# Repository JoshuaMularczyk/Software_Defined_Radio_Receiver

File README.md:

# Software-Defined-Radio-Reciever

This project was taken on with the goal to create a Software Defined Radio (SDR) in coolaboration with my partner [Christian Williams](https://github.com/cwill713). This project was completed for my Engineering Electronics II class and given to us by our professor, [Dr. Rob Frohne](https://github.com/frohro).

## Design Specifications/Objectives

These are the design specifications and objectives that my partner and I decided on. Origianlly, we decided to build a commercial FM radio, but after discusstion with Dr. Frohne, we reconsidered. The final specifications we decided on are as follows:

#### Objectives

- $25 budget
- Less than -107 dBm (1uV) minimum discernible signal
- *Stretch Goal* -127 dBm (.1uV) minimum discernible signal
- Good image rejection
- Low noise figure

#### Specs

- Frequency Range: 7MHz - 18MHz
- Radio Type: Shortwave
- One Butterworth Bandpass Filter
- One Tayloe Mixer
- One Bessel Lowpass Filter
- One Power Supply Noise Filter

## Overview

Our (SDR) receiver connects to an antenna (mounted ontop of the Engineering Building) and covers the filtering, mixing, and amplifying of the desired I and Q signals. Our I and Q signals are then passed through an external sound card and software handles the demodulation of the signal into audio. The mixing in our SDR is handled using an Arduino Nano running code provided to us by Dr. Rob Frohne which can be found in the [Arduino file](https://github.com/JoshuaMularczyk/Software_Defined_Radio_Receiver/blob/main/Arduino/New_Quisk_Nano/New_Quisk_Nano.ino). The Arduino interfaces with Quisk, an SDR that controls our receiver through the Arduino. Using Quisk, the radio can be tuned to a certain frequency by adjusting the speed of the local oscillator used in the mixing process.

## Theory

The block diagram above shows the basic components of our SDR Receiver. The signal is received by an antenna and is passed through the bandpass filter which attenuates signals that are above or below our frequency range of 7-18 MHz. These signals are then passed through the Tayloe Quadrature Product Detector. This generates the I and Q signals for demodulation. Once the signals have been split they pass through the low noise filter which cuts off anything above 100 KHz, creating a smooth output signal. This signal is then send into an external soundcard which demodulates teh signal before it is read by Quisk software. Quisk interfaces to the Arduino Nana and allows for tuning of the desired frequency.

## Rev 6 Schematic

Christian and I built and tested our SDR based on the 5th Rev of this project. These schematics can be found in the Rev 5 file. The follow schematics are our most updated designs. These were created after finding multiple errors while constructing our pcb. The Rev 6 schematics can be downloaded [here](https://github.com/JoshuaMularczyk/Software_Defined_Radio_Receiver/tree/main/Schematics/SDRrecV6). These schematics were all designed in [KiCad](https://www.kicad.org/) and will be broken down into seperate pieces below.

### BandPass Filter

We built this bandpass filter using the [LC Filter Design Tool](https://rf-tools.com/lc-filter/.). This is a 3rd-Order Conventional, Series First, Butterworth Filter that will only allow frequencies between 7MHz and 18MHz to pass through it. It has input and output impedances of 50 ohms.

### Mixer and Lowpass Filter

The mixer that Christian and I decided to use was  Tayloe Mixer we referenced this [paper](http://www.norcalqrp.org/files/Tayloe_mixer_x3a.pdf) by Dan Tayloe when designing our mixer. The demultiplexer that we used was the [SN74CBT](http://www.ti.com/lit/gpn/sn74cbt3253) which converts the RF signal into four baseband signals. The Tayloe mixer uses switches to combine the signals that are 180 degrees out of phase with differential amplifiers so that signals above and below the oscilator frequecy can be detected.

Our Lowpass filter was designed using the [TI Filter Design Tool](). It was made using two [LT6231](https://www.analog.com/media/en/technical-documentation/data-sheets/623012fc.pdf) low noise op amps and is designed to block all frequencies greater that 100kHz.

### Voltage Smoother

Our Voltage Smoother with take the 5V Vcc and remove as much noise as possible using a very large capacitace. Our schematic here shows the C3 having a value of 8200uF, however we ended up using a 1F capacitor that we already had in the lab. This takes the voltage that comes in from the computer and outputs a smoother 5V for the SDR to use.

### Arduino and Si5351

Our [Si5351](https://www.silabs.com/documents/public/data-sheets/Si5351-B.pdf) programmable oscillator allows us to input two clock signals that are 90 degrees out of phase into S0 and S1 of the SN74CBT3253. The Arduino Nano controls the frequency that is put out by the Si5351 for tuning. For our testing we had the [Aduino](http://www.mouser.com/pdfdocs/Gravitech_Arduino_Nano3_0.pdf) set the frequency to 14,190,000 Hz to match what was being output by a signal generator.

## Rev 5 Simulations

We conducted all of our simulations on [LTSpice](https://www.analog.com/en/design-center/design-tools-and-calculators/ltspice-simulator.html). My partner, Christian Williams, conducted the simulations of both filters and the Tayloe Mixer.

### Bandpass Filter

Our Bandpass Filter was designed to allow a frequency range of 7-18MHz to pass through. As seen in the simulation above, curser 1 and cursor 2 mark the two freqency cutoff points. Inbetween them is the peak of our curve which is just where we want it.

### Lowpass Filter

### Complete SDR

We designed the tayloe mixer using four voltage controlled switches, and four voltage pulses that control them. For our op amps, we added our LT6231, these are already Linear Technology componenets so they dont take long to simulate in LTSpice. The LT6231's had a much lower noise profile than the LM4578's we selected for our second LPF(which we ended up removing in Rev 6), so we knew that the first LPF would take care of mostly everything and the second would just perfect the output. In the simulation window above you can see the baseband signals and the I and Q outputs. They're exactly as expected, about 90 degrees out of phase.

## Rev 6 PCB Design

## Rev 5 Testing and Fixed Issues

When constructing our Rev 5 board, I ran into three issues. These issues have been fixed and closed. They are explained in detail in the issues page [here](https://github.com/JoshuaMularczyk/Software_Defined_Radio_Receiver/issues?q=is%3Aissue+is%3Aclosed)!

Luckily I was able to fix all of these mistakes with simple cutting and jumping techniques. We immediately fixed the schematics and Christian created Rev 6 of the PCB which was displayed above.

## Project Results

We first tested to see the minimum discernible signal by hooking our board up to a signal generator, our system running quisk software, and a soundcard. We adjusted the attenuator on the signal generator to output a signal of 14.19 MHz and then dropped the signal on the attenuator to see how small of a signal we could detect. In the image below, we see our radio has a minimum disernable signal of inbetween 0.3-0.4 uV!

We then hooked up our SDR to a BNC connector that ran to the roof of our Engineering building into an antenna. The final test was to see if we could hear any radio opperators transmitting around the world. We first looked at the signals being read in to see that our radio was picking up signals as far as Russia and Italy. Next we decided to listen in and found several bandwidths being used for communications. Here are two that we took snippets of.

The first signal that we tuned into was being used to communicate the weather from what sounded like an air traffic control tower. 

## "Wind 360 degrees, light drizzle, visibility more than 6 miles".

The second was an automated message that would read off the Coordinated Universal time every minute.

## "At the tone ****** 5 hours 52 minutes coordinated universal time"

We were also able to listen to a few different music stations as well as two men in Hawaii talk about hurricanes to each other.

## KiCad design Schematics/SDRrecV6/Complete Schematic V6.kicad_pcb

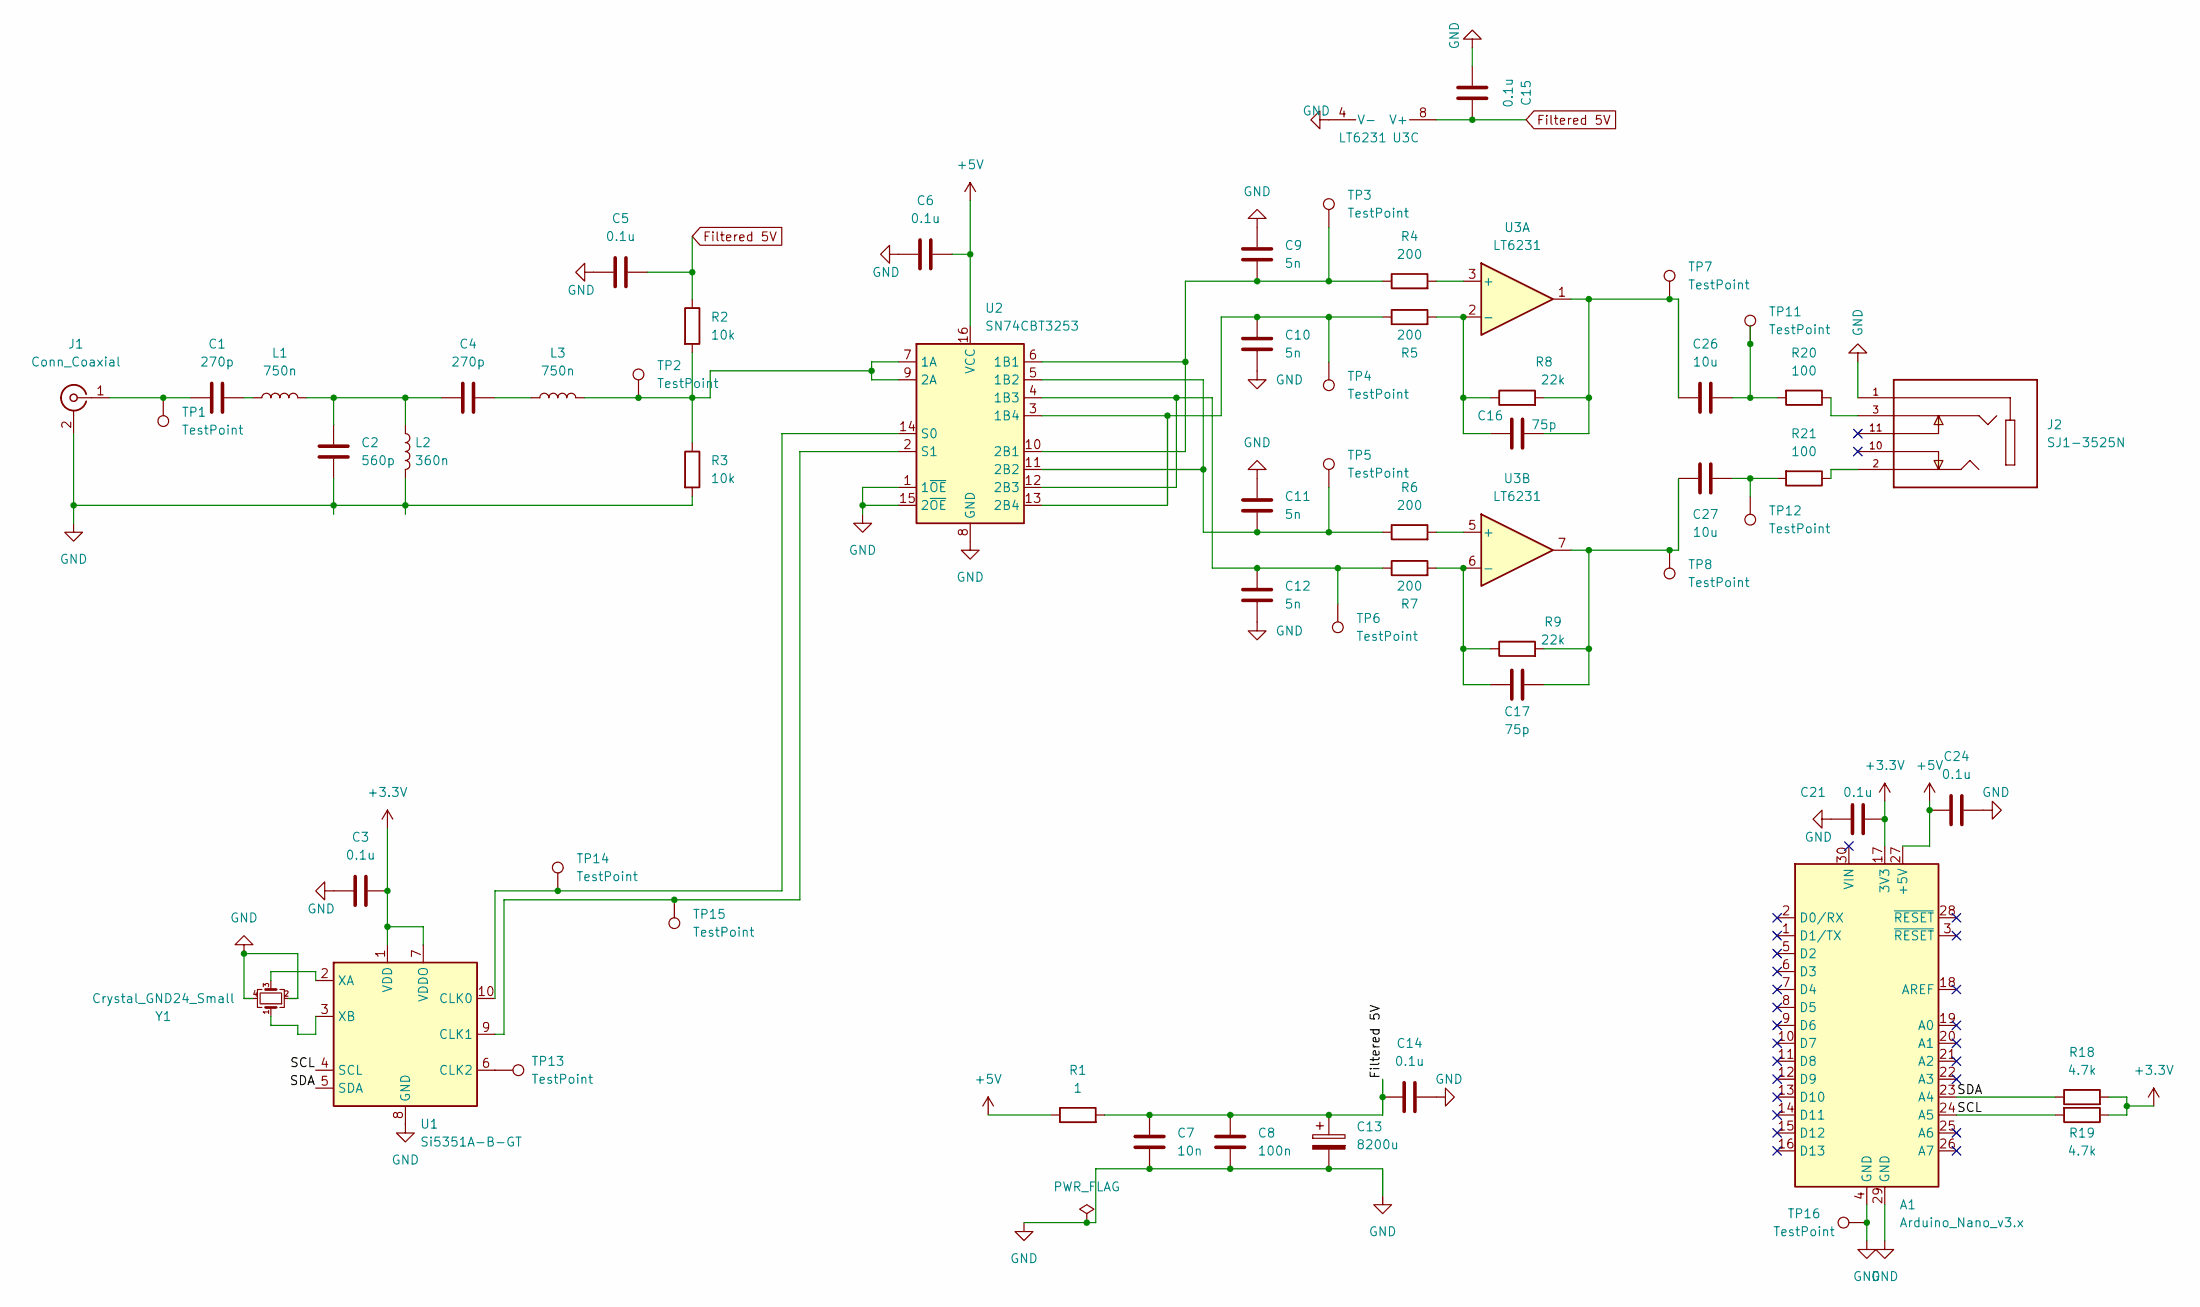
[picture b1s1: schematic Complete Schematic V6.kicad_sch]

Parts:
A1: Arduino_Nano_v3.x; Arduino_Nano
C1, C4: 270p; C_0805_2012Metric
C2: 560p; C_0805_2012Metric
C3, C5, C6, C14, C15, C21, C24: 0.1u; C_0805_2012Metric
C7: 10n; C_0805_2012Metric
C8: 100n; C_0805_2012Metric
C9, C10, C11, C12: 5n; C_0805_2012Metric
C13: 8200u; CP_Radial_D16.0mm_P7.50mm
C16, C17: 75p; C_0805_2012Metric
C26, C27: 10u; C_0805_2012Metric
J1: Conn_Coaxial; BNC_Amphenol_B6252HB-NPP3G-50_Horizontal
J2: SJ1-3525N; CUI_SJ1-3525N; PARTREV 1.02
L1, L3: 750n; L_Toroid_Vertical_L10.0mm_W5.0mm_P5.08mm
L2: 360n; L_Toroid_Vertical_L10.0mm_W5.0mm_P5.08mm
R1: 1; R_0805_2012Metric
R2, R3: 10k; R_0805_2012Metric
R4, R5, R6, R7: 200; R_1206_3216Metric
R8, R9: 22k; R_0805_2012Metric
R18, R19: 4.7k; R_0805_2012Metric
R20, R21: 100; R_0805_2012Metric
TP1, TP2, TP3, TP4, TP5, TP6, TP7, TP8, TP11, TP12, TP13, TP14, TP15, TP16: TestPoint; TestPoint_THTPad_2.0x2.0mm_Drill1.0mm
U1: Si5351A-B-GT; MSOP-10_3x3mm_P0.5mm
U2: SN74CBT3253; SOIC-16_3.9x9.9mm_P1.27mm
U3: LT6231; SOIC-8_3.9x4.9mm_P1.27mm
Y1: Crystal_GND24_Small; Crystal_SMD_3225-4Pin_3.2x2.5mm

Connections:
+3V3: A1.17 (3V3), C3.2, C21.2, R18.2, R19.1, U1.1 (VDD), U1.7 (VDDO)
+5V: A1.27 (+5V), C6.2, C24.2, R1.1, U2.16 (VCC)
/SCL: A1.24 (A5), R19.2, U1.4 (SCL)
/SDA: A1.23 (A4), R18.1, U1.5 (SDA)
Filtered 5V: C5.2, C7.1, C8.1, C13.1, C14.2, C15.2, R1.2, R2.1, U3.8 (V+)
GND: A1.4 (GND), A1.29 (GND), C2.2, C3.1, C5.1, C6.1, C7.2, C8.2, C9.2, C10.1, C11.2, C12.1, C13.2, C14.1, C15.1, C21.1, C24.1, J1.2 (Ext), J2.1, L2.2, R3.2, TP16.1, U1.8 (GND), U2.1 (1~OE), U2.8 (GND), U2.15 (2~OE), U3.4 (V-), Y1.2, Y1.4
unnamed: C1.1, L1.1
unnamed: C1.2, J1.1 (In), TP1.1
unnamed: C2.1, C4.1, L1.2, L2.1
unnamed: C4.2, L3.1
unnamed: C9.1, R4.1, TP3.1, U2.6 (1B1), U2.10 (2B1)
unnamed: C10.2, R5.1, TP4.1, U2.3 (1B4), U2.13 (2B4)
unnamed: C11.1, R6.1, TP5.1, U2.5 (1B2), U2.11 (2B2)
unnamed: C12.2, R7.1, TP6.1, U2.4 (1B3), U2.12 (2B3)
unnamed: C16.1, C26.2, R8.2, TP7.1, U3.1
unnamed: C16.2, R5.2, R8.1, U3.2 (-)
unnamed: C17.1, C27.2, R9.2, TP8.1, U3.7
unnamed: C17.2, R7.2, R9.1, U3.6 (-)
unnamed: C26.1, R20.2, TP11.1
unnamed: C27.1, R21.2, TP12.1
unnamed: J2.2, R21.1
unnamed: J2.3, R20.1
unnamed: L3.2, R2.2, R3.1, TP2.1, U2.7 (1A), U2.9 (2A)
unnamed: R4.2, U3.3 (+)
unnamed: R6.2, U3.5 (+)
unnamed: TP13.1, U1.6 (CLK2)
unnamed: TP14.1, U1.10 (CLK0), U2.14 (S0)
unnamed: TP15.1, U1.9 (CLK1), U2.2 (S1)
unnamed: U1.2 (XA), Y1.3
unnamed: U1.3 (XB), Y1.1

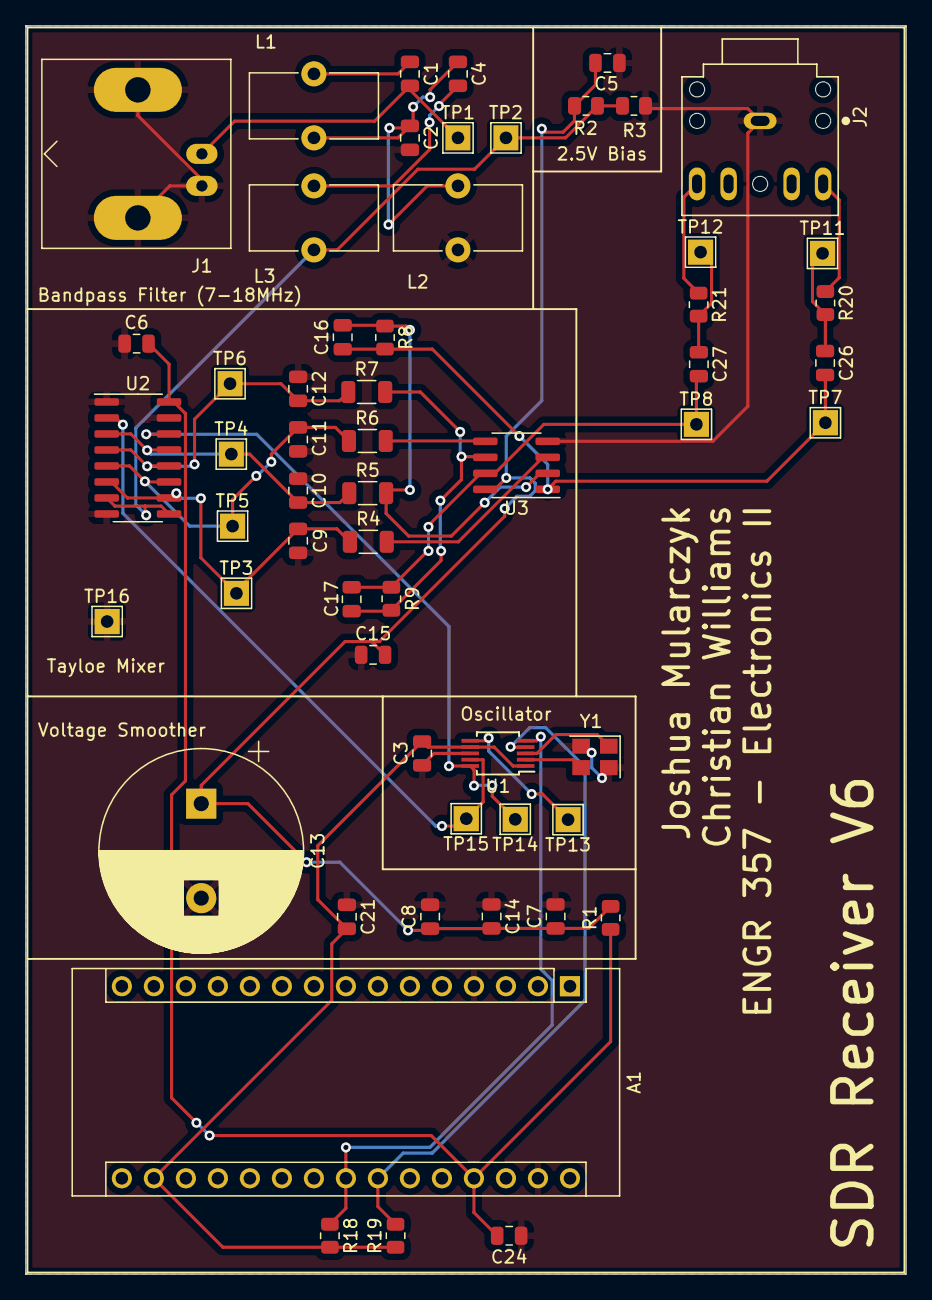
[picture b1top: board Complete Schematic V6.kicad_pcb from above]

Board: 2 copper layers, 69.9 x 99.1 mm, 58 parts (0 on the bottom side), 30 nets.

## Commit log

2022-04-19 Upload of LowPass Filter LTSpice sim
2022-04-19 Upload of seperate part schematics from KiCad
2022-04-25 added parts list
2022-06-06 Complete upload of all project files
2022-06-06 Clean up of files
2022-06-06 Renaming
2022-06-15 Added visuals
2022-06-22 Create LICENSE
    Created license for electronics 2 class
